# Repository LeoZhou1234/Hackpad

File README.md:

# Leo's Hackpad #

My submission for Hack Club Blueprint.<br>

## Features ##
- 16 keys arranged in a 4x4 matrix
- Rotary encoder for volume control
- Rotary encoder doubles as a play/pause button
- USB-C connectivity
- 3D Printed Case

## Case ##
The case consists of three parts: the top, bottom, and switch plate. 
The three parts are secured with M3x16mm bolts and heat set inserts. Refer to the images below for assembly.
Designed in Onshape.<br>

## PCB ##
The PCB contains a 4x4 column to row matrix for the switches, with an extra column added for the switch on the rotary encoder. The encoder used is an EC11.
The matrix uses 1N4148 diodes to prevent ghosting. 
A through-hole mounted Seeed Studio XIAO RP2040 serves as the controller.
Designed in KiCad.<br>

## Firmware ##
The firmware is QMK. The keymap is currently configured as a numpad.

```            
            ┌───┐
            │Vol│
┌───┬───┬───┼───┤
│ 7 │ 8 │ 9 │ / │
├───┼───┼───┼───┤
│ 4 │ 5 │ 6 │ * │
├───┼───┼───┼───┤
│ 1 │ 2 │ 3 │ - │
├───┼───┼───┼───┤
│ 0 │ . │Ent│ + │
└───┴───┴───┴───┘
```
The rotary encoder is located where `vol` is. It works as volume control when rotated (CW - Vol Up / CCW - Vol Down), and can play/pause when pressed.<br>

## BOM ##

- 4x M3x16mm SCHS Bolts
- 4x M3x⌀5mmx4mm Heat Set Inserts
- 16x Cherry MX Style Switches
- 16x 1U Keycaps
- 1x EC11 Rotary Encoder
- 1x 3D Printed Knob 
- 17x 1N4148 DO-35 Diodes
- 1x Seeed Studio XIAO RP2040
- 1x PCB
- 1x 3D Printed Case
    - Case Top
    - Case Bottom
    - Switch Plate

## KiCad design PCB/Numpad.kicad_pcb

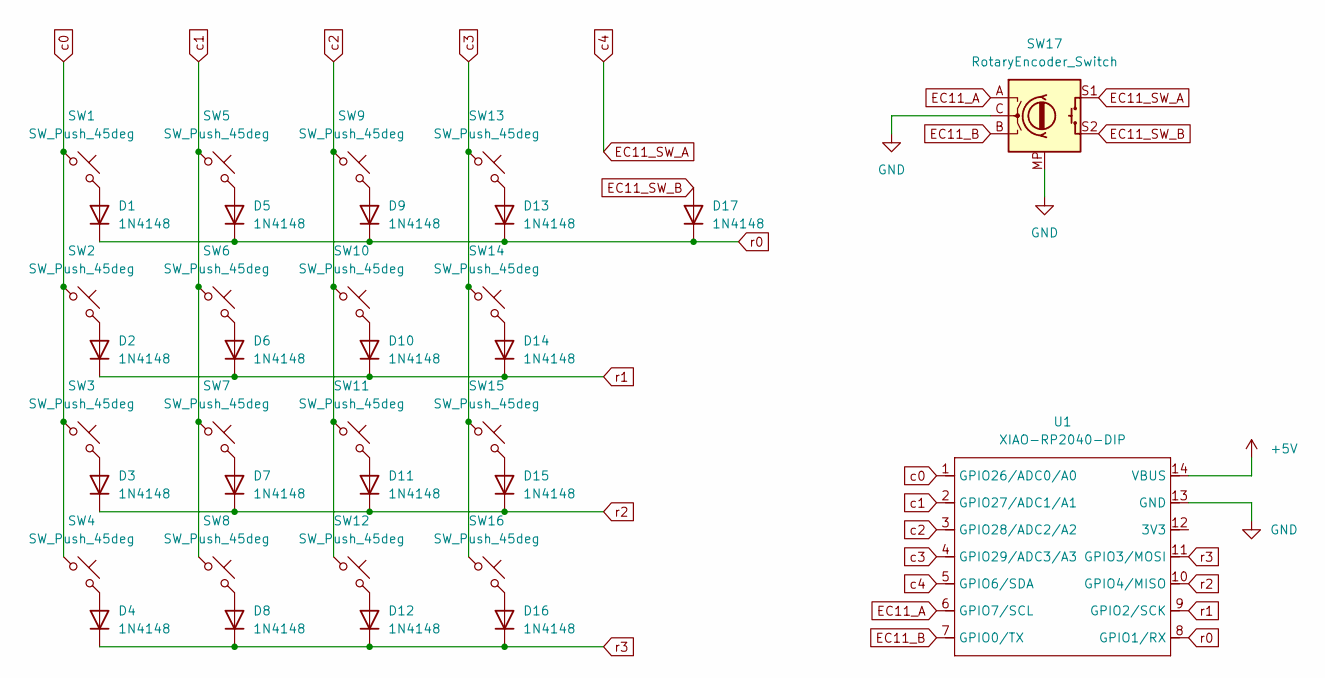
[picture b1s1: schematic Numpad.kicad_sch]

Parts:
D1, D2, D3, D4, D5, D6, D7, D8, D9, D10, D11, D12, D13, D14, D15, D16, D17: 1N4148; D_DO-35_SOD27_P7.62mm_Horizontal
SW1, SW2, SW3, SW4, SW5, SW6, SW7, SW8, SW9, SW10, SW11, SW12, SW13, SW14, SW15, SW16: SW_Push_45deg; SW_Cherry_MX_1.00u_PCB
SW17: RotaryEncoder_Switch; RotaryEncoder_Alps_EC11E-Switch_Vertical_H20mm
U1: XIAO-RP2040-DIP

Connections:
+5V: U1.14 (VBUS)
EC11_A: SW17.A, U1.6 (GPIO7/SCL)
EC11_B: SW17.B, U1.7 (GPIO0/TX)
EC11_SW_A: SW17.S1, U1.5 (GPIO6/SDA)
EC11_SW_B: D17.2 (A), SW17.S2
GND: SW17.C, SW17.MP, U1.13 (GND)
unnamed: D1.2 (A), SW1.2
unnamed: D2.2 (A), SW2.2
unnamed: D3.2 (A), SW3.2
unnamed: D4.2 (A), SW4.2
unnamed: D5.2 (A), SW5.2
unnamed: D6.2 (A), SW6.2
unnamed: D7.2 (A), SW7.2
unnamed: D8.2 (A), SW8.2
unnamed: D9.2 (A), SW9.2
unnamed: D10.2 (A), SW10.2
unnamed: D11.2 (A), SW11.2
unnamed: D12.2 (A), SW12.2
unnamed: D13.2 (A), SW13.2
unnamed: D14.2 (A), SW14.2
unnamed: D15.2 (A), SW15.2
unnamed: D16.2 (A), SW16.2
c0: SW1.1, SW2.1, SW3.1, SW4.1, U1.1 (GPIO26/ADC0/A0)
c1: SW5.1, SW6.1, SW7.1, SW8.1, U1.2 (GPIO27/ADC1/A1)
c2: SW9.1, SW10.1, SW11.1, SW12.1, U1.3 (GPIO28/ADC2/A2)
c3: SW13.1, SW14.1, SW15.1, SW16.1, U1.4 (GPIO29/ADC3/A3)
r0: D1.1 (K), D5.1 (K), D9.1 (K), D13.1 (K), D17.1 (K), U1.8 (GPIO1/RX)
r1: D2.1 (K), D6.1 (K), D10.1 (K), D14.1 (K), U1.9 (GPIO2/SCK)
r2: D3.1 (K), D7.1 (K), D11.1 (K), D15.1 (K), U1.10 (GPIO4/MISO)
r3: D4.1 (K), D8.1 (K), D12.1 (K), D16.1 (K), U1.11 (GPIO3/MOSI)

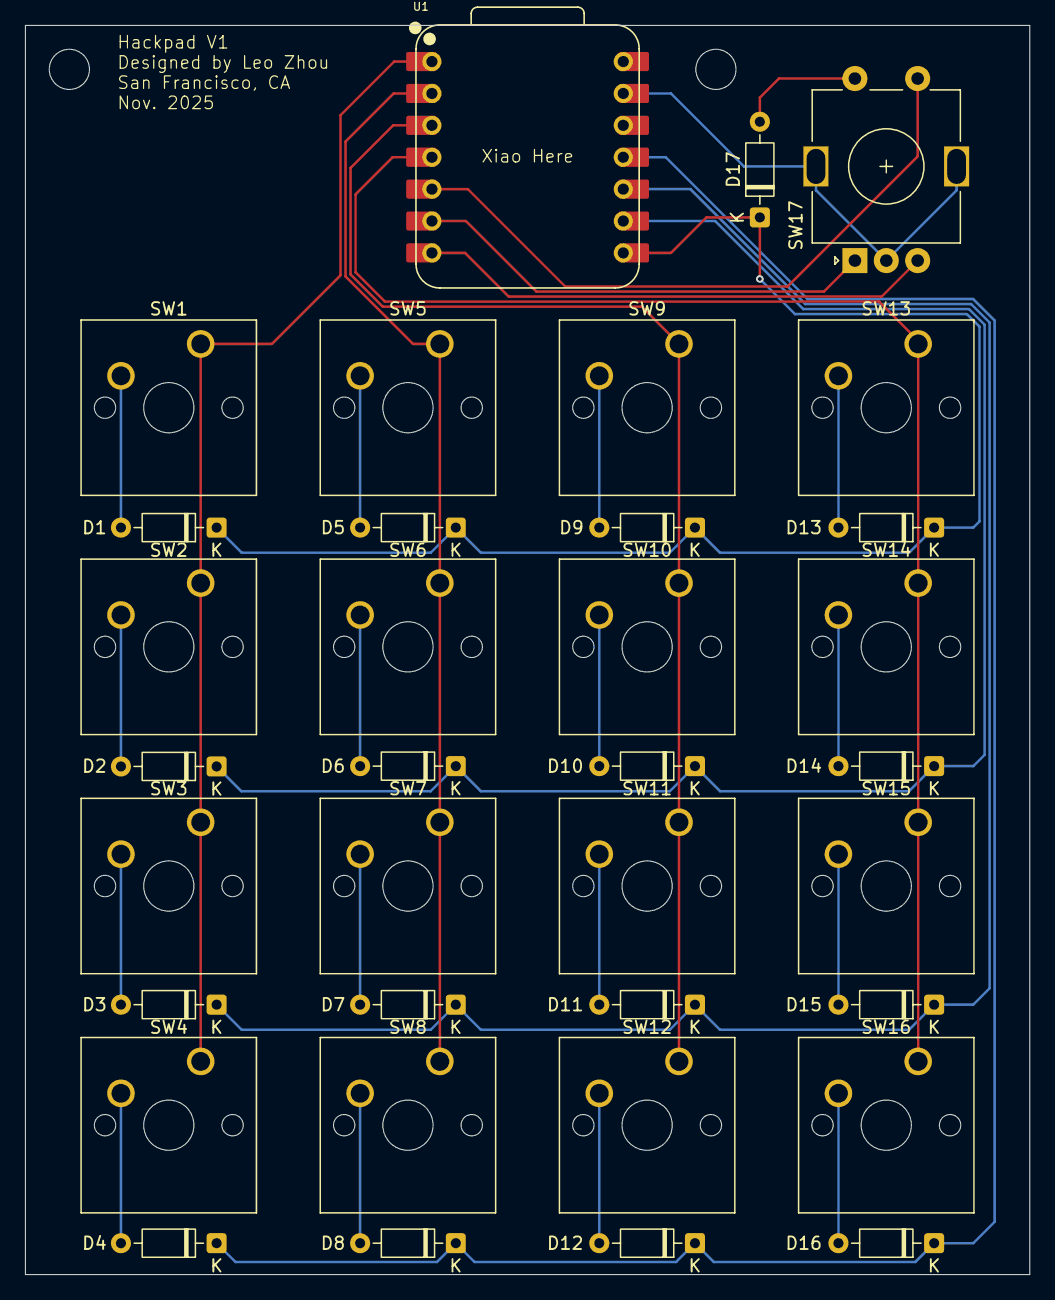
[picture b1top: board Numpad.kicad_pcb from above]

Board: 2 copper layers, 80.0 x 99.5 mm, 35 parts (0 on the bottom side), 29 nets.

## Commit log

2025-12-14 finished readme
2025-12-14 fixed formatting in readme
2025-12-14 fixed typo
2025-12-14 polishing
2025-12-14 added pcb to bom
    Removed duplicate entry for 3D Printed Knob.
